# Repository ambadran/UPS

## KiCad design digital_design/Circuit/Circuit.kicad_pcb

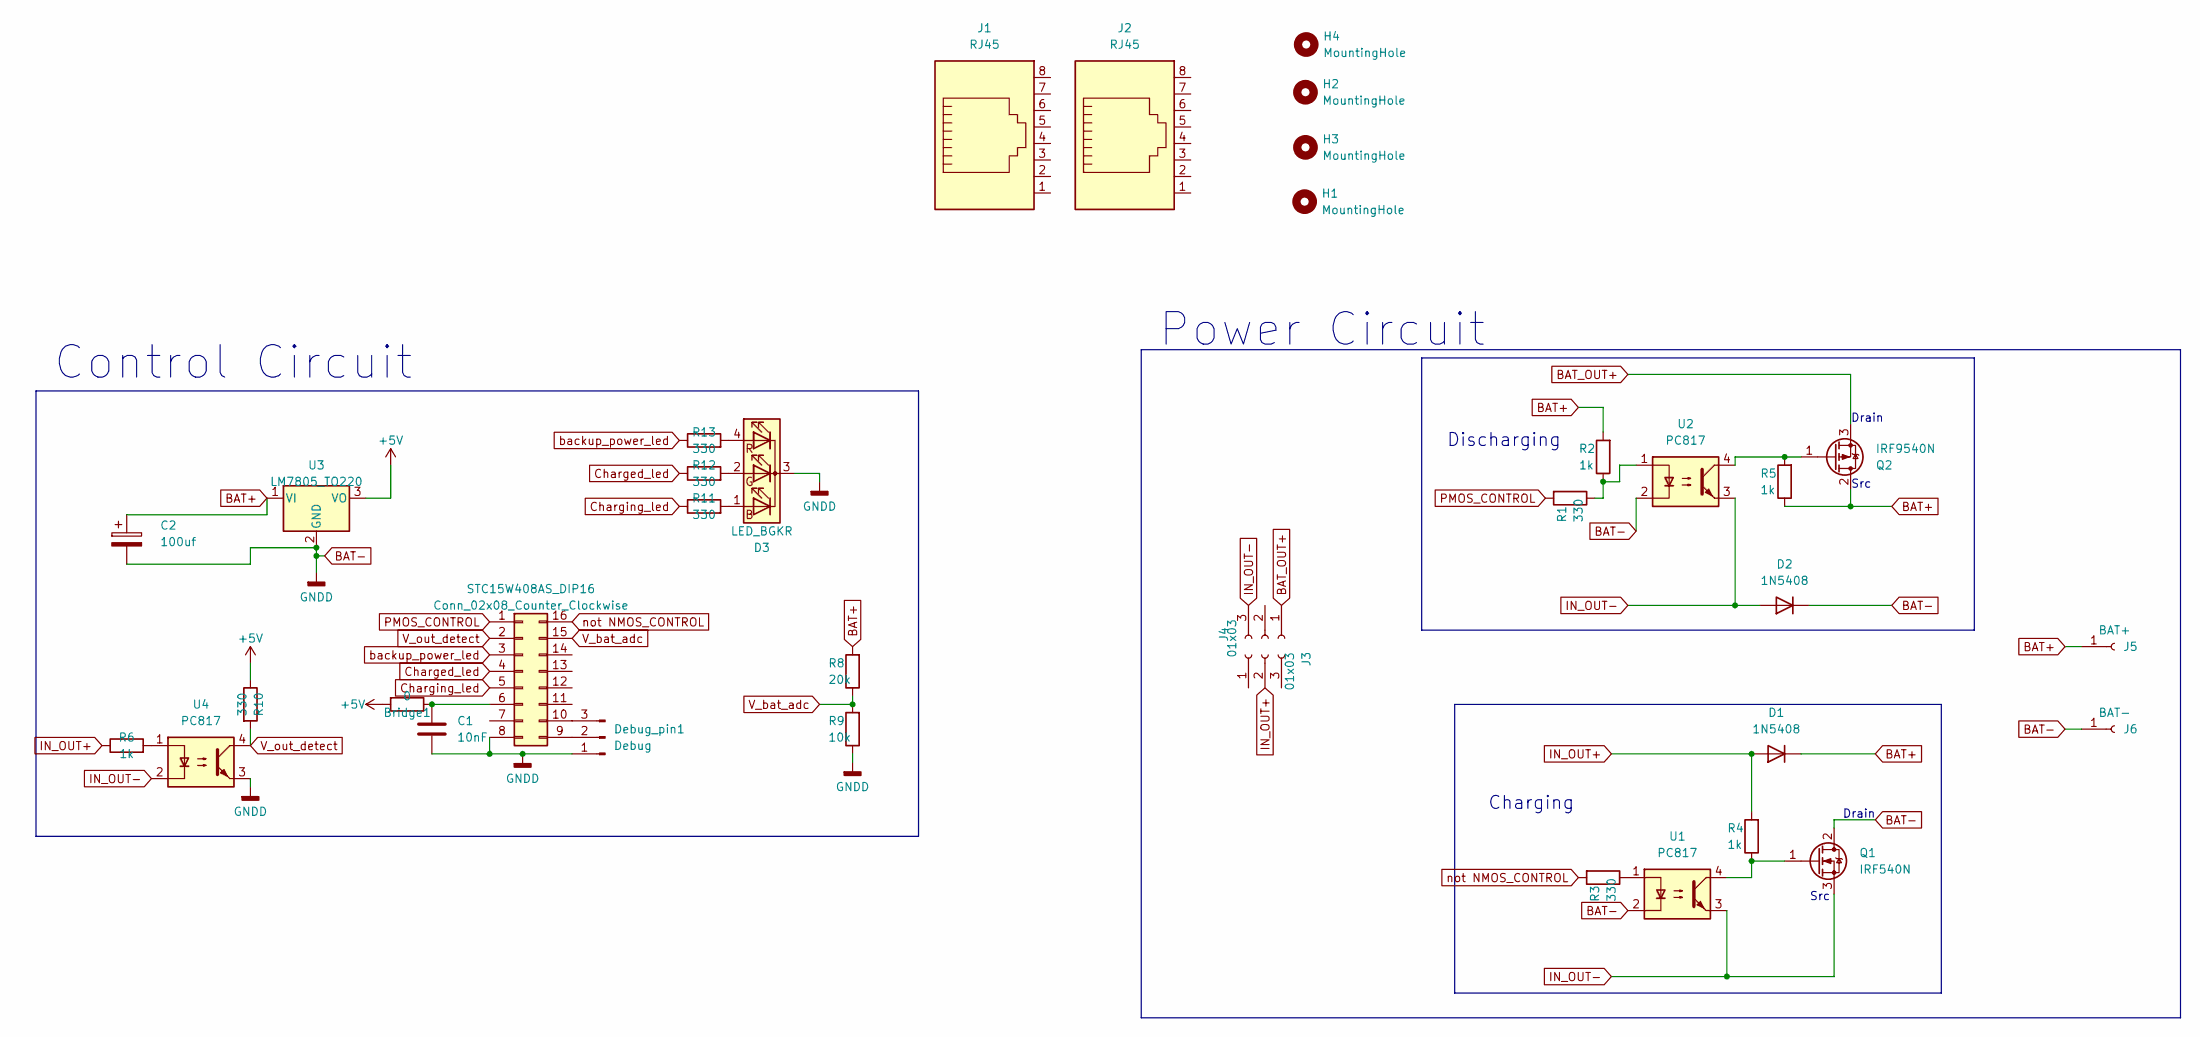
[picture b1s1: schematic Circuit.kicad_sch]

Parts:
Bridge1: 0; R_Axial_DIN0207_L6.3mm_D2.5mm_P7.62mm_Horizontal
C1: 10nF; C_Disc_D5.0mm_W2.5mm_P2.50mm
C2: 100uf; CP_Radial_D5.0mm_P2.50mm
D1, D2: 1N5408; D_DO-201AD_P15.24mm_Horizontal
D3: LED_BGKR; PinSocket_1x04_P2.54mm_Vertical
Debug_pin1: Debug; PinSocket_1x03_P2.54mm_Vertical
H1, H2, H3, H4: MountingHole; MountingHole_4mm_Pad_TopBottom
J1, J2: RJ45; RJ45_OST_PJ012-8P8CX_Vertical
J3, J4: 01x03; SolderWire-0.1sqmm_1x03_P3.6mm_D0.4mm_OD1mm
J5: BAT+; MountingHole_3.2mm_M3_DIN965_Pad_TopBottom
J6: BAT-; MountingHole_3.2mm_M3_DIN965_Pad_TopBottom
Q1: IRF540N; TO-220-3_Vertical
Q2: IRF9540N; TO-220-3_Vertical
R1, R10, R12, R13: 330; R_Axial_DIN0207_L6.3mm_D2.5mm_P7.62mm_Horizontal
R2, R4, R5, R6: 1k; R_Axial_DIN0207_L6.3mm_D2.5mm_P7.62mm_Horizontal
R3, R11: 330; R_Axial_DIN0207_L6.3mm_D2.5mm_P10.16mm_Horizontal
R8: 20k; R_Axial_DIN0207_L6.3mm_D2.5mm_P7.62mm_Horizontal
R9: 10k; R_Axial_DIN0207_L6.3mm_D2.5mm_P7.62mm_Horizontal
STC15W408AS_DIP16: Conn_02x08_Counter_Clockwise; CERDIP-16_W7.62mm_SideBrazed_LongPads
U1, U2, U4: PC817; DIP-4_W7.62mm
U3: LM7805_TO220; TO-220-3_Vertical

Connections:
+5V: Bridge1.2, R10.1, U3.3 (VO)
BAT+: C2.1, D1.1 (K), J5.1, Q2.2 (D), R2.2, R5.1, R8.2, U3.1 (VI)
BAT-: C1.2, C2.2, D2.1 (K), D3.3 (K), Debug_pin1.1, J6.1, Q1.2 (D), R9.1, STC15W408AS_DIP16.8, U1.2, U2.2, U3.2 (GND), U4.3
BAT_OUT+: J4.1, Q2.3 (S)
Charged_led: R12.1, STC15W408AS_DIP16.4
Charging_led: R11.1, STC15W408AS_DIP16.5
IN_OUT+: D1.2 (A), J3.2, R4.2, R6.1
IN_OUT-: D2.2 (A), J4.3, Q1.3 (S), U1.3, U2.3, U4.2
unnamed: D3.1 (BA), R11.2
unnamed: D3.2 (GA), R12.2
unnamed: D3.4 (RA), R13.2
unnamed: Debug_pin1.2, STC15W408AS_DIP16.9
unnamed: Debug_pin1.3, STC15W408AS_DIP16.10
unnamed: Q1.1 (G), R4.1, U1.4
unnamed: Q2.1 (G), R5.2, U2.4
unnamed: R1.1, R2.1, U2.1
unnamed: R3.1, U1.1
unnamed: R6.2, U4.1
unnamed: Bridge1.1, C1.1, STC15W408AS_DIP16.6
PMOS_CONTROL: R1.2, STC15W408AS_DIP16.1
V_bat_adc: R8.1, R9.2, STC15W408AS_DIP16.15
V_out_detect: R10.2, STC15W408AS_DIP16.2, U4.4
backup_power_led: R13.1, STC15W408AS_DIP16.3
not NMOS_CONTROL: R3.2, STC15W408AS_DIP16.16

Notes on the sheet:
Src
Power Circuit
Drain
Control Circuit
Discharging
Charging

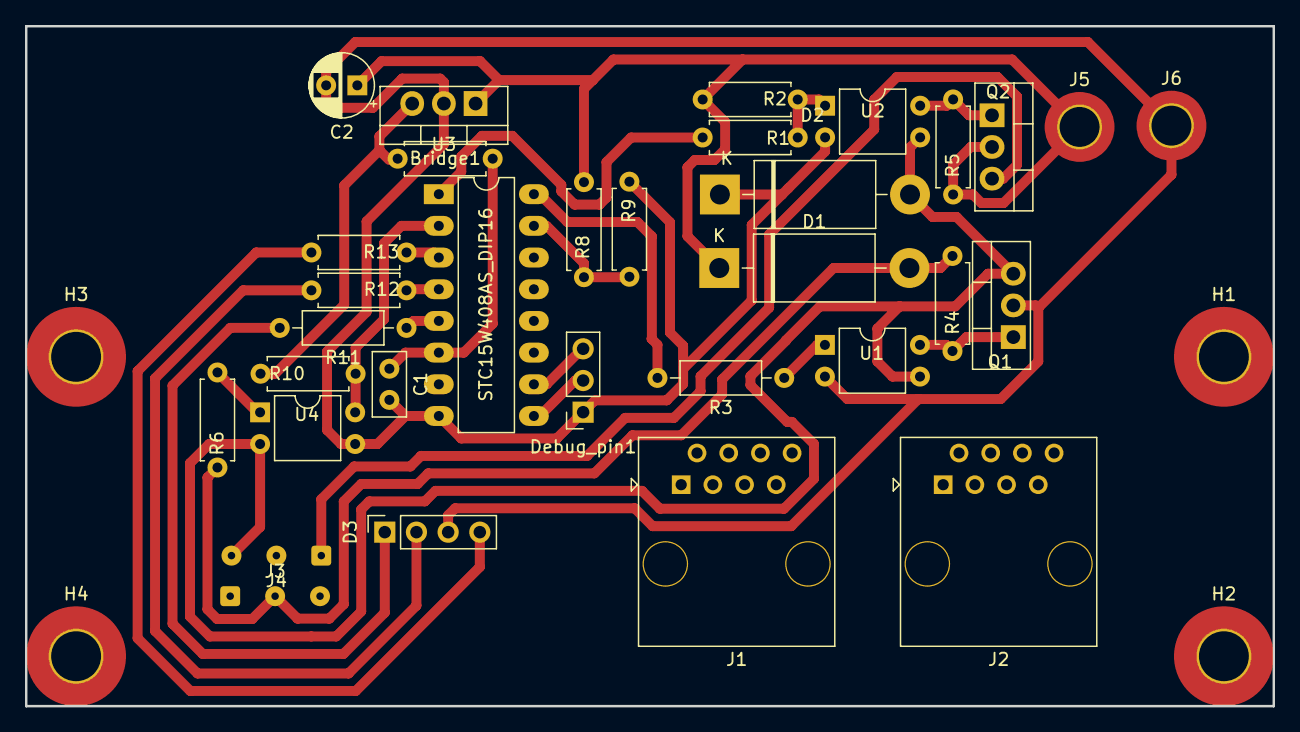
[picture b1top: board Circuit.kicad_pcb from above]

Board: 2 copper layers, 100.0 x 54.5 mm, 36 parts (0 on the bottom side), 24 nets.

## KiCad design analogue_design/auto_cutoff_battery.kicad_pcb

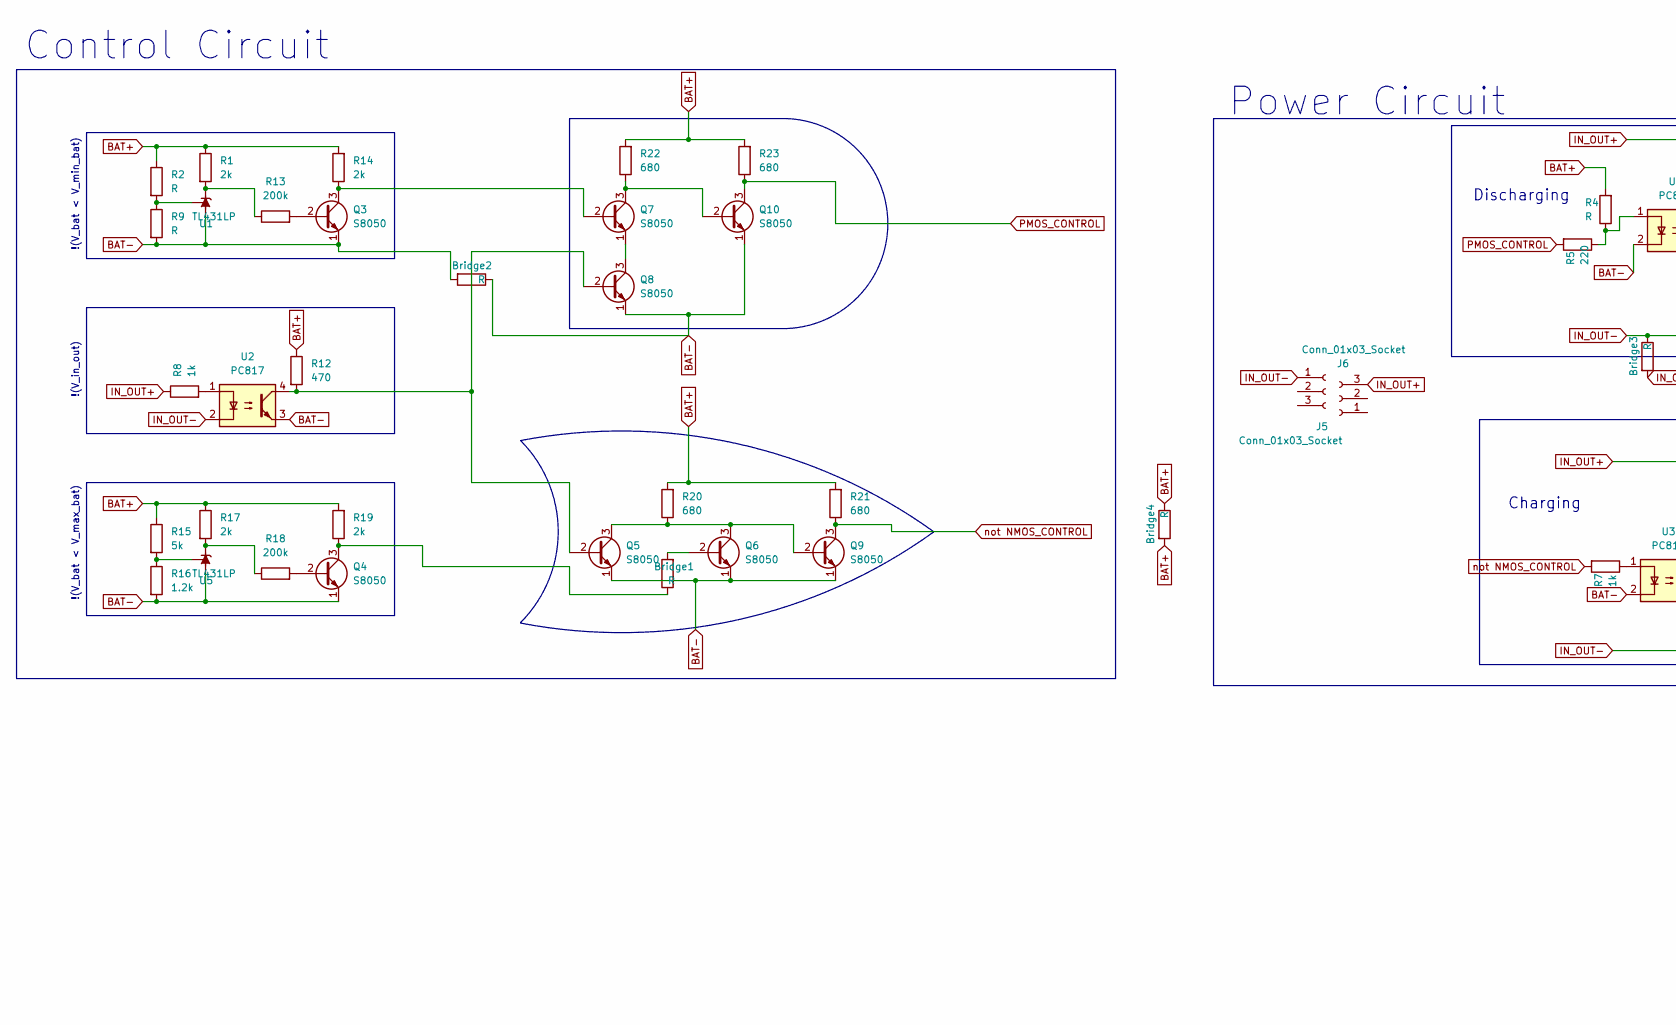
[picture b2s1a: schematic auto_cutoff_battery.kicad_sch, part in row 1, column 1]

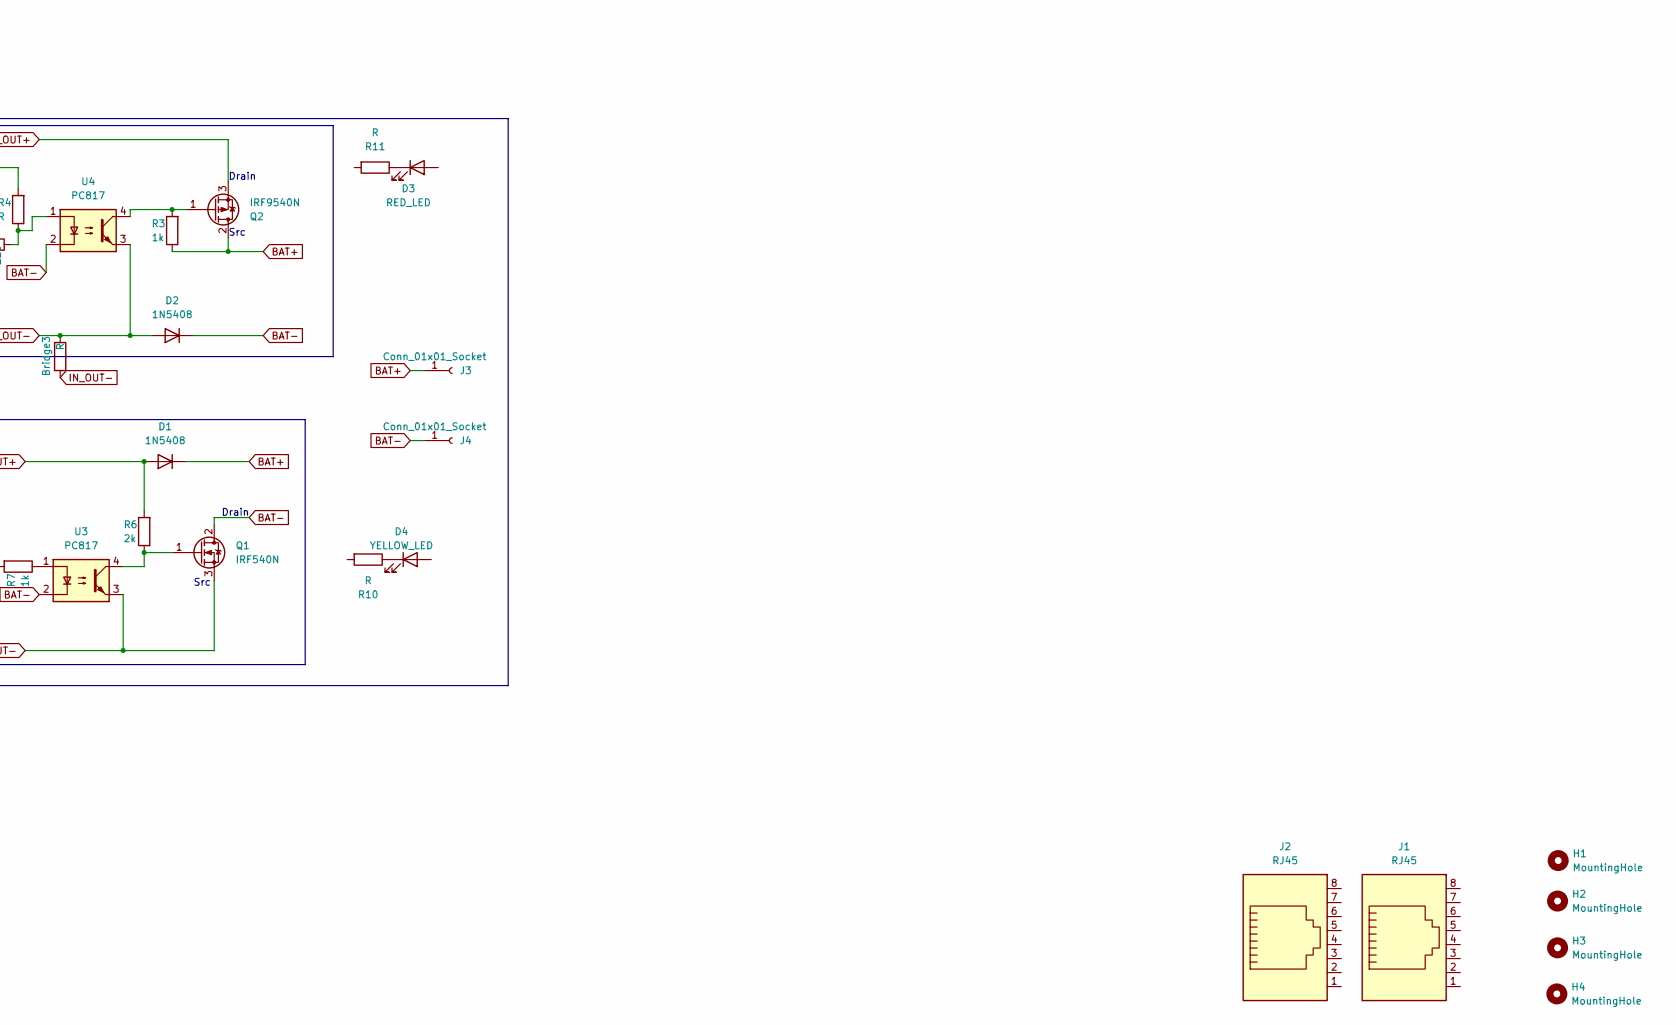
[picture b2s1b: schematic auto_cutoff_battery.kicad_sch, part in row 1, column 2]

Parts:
Bridge1, Bridge2, Bridge3: R; R_Axial_DIN0207_L6.3mm_D2.5mm_P5.08mm_Vertical
Bridge4: R; R_Axial_DIN0207_L6.3mm_D2.5mm_P7.62mm_Horizontal
D1, D2: 1N5408; D_DO-201AD_P15.24mm_Horizontal
D3: RED_LED; LED_D3.0mm
D4: YELLOW_LED; LED_D3.0mm
H1, H2, H3, H4: MountingHole; MountingHole_5.3mm_M5_DIN965_Pad
J1, J2: RJ45; RJ45_Molex_0855135013_Vertical
J3, J4: Conn_01x01_Socket; PinSocket_1x01_P2.54mm_Vertical
J5, J6: Conn_01x03_Socket; SolderWire-0.1sqmm_1x03_P3.6mm_D0.4mm_OD1mm
Q1: IRF540N; TO-220-3_Vertical
Q2: IRF9540N; TO-220-3_Vertical
Q3, Q4, Q5, Q6, Q7, Q8, Q9, Q10: S8050; TO-92_Inline_Wide
R1, R6, R14, R17, R19: 2k; R_Axial_DIN0207_L6.3mm_D2.5mm_P7.62mm_Horizontal
R2, R4, R9, R10, R11: R; R_Axial_DIN0207_L6.3mm_D2.5mm_P7.62mm_Horizontal
R3, R7, R8: 1k; R_Axial_DIN0207_L6.3mm_D2.5mm_P7.62mm_Horizontal
R5: 220; R_Axial_DIN0207_L6.3mm_D2.5mm_P7.62mm_Horizontal
R12: 470; R_Axial_DIN0207_L6.3mm_D2.5mm_P7.62mm_Horizontal
R13, R18: 200k; R_Axial_DIN0207_L6.3mm_D2.5mm_P7.62mm_Horizontal
R15: 5k; R_Axial_DIN0207_L6.3mm_D2.5mm_P7.62mm_Horizontal
R16: 1.2k; R_Axial_DIN0207_L6.3mm_D2.5mm_P7.62mm_Horizontal
R20, R21, R22, R23: 680; R_Axial_DIN0207_L6.3mm_D2.5mm_P7.62mm_Horizontal
U1, U5: TL431LP; TO-92_Inline_Wide
U2, U3, U4: PC817; DIP-4_W7.62mm

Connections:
BAT+: Bridge4.1, Bridge4.2, D1.1 (K), J3.1, Q2.2 (D), R1.1, R2.1, R3.1, R4.2, R12.1, R14.2, R15.1, R17.1, R19.2, R20.2, R21.2, R22.2, R23.2
BAT-: Bridge2.1, Bridge2.2, D2.1 (K), J4.1, Q1.2 (D), Q3.1 (E), Q4.1 (E), Q5.1 (E), Q6.1 (E), Q8.1 (E), Q9.1 (E), Q10.1 (E), R9.2, R16.2, U1.2 (A), U2.3, U3.2, U4.2, U5.2 (A)
IN_OUT+: D1.2 (A), J6.3, Q2.3 (S), R6.2, R8.1
IN_OUT-: Bridge3.1, Bridge3.2, D2.2 (A), J5.1, Q1.3 (S), U2.2, U3.3, U4.3
unnamed: D3.1 (K), R11.1
unnamed: D4.1 (K), R10.1
unnamed: Q1.1 (G), R6.1, U3.4
unnamed: Q2.1 (G), R3.2, U4.4
unnamed: Q3.2 (B), R13.2
unnamed: Q3.3 (C), Q7.2 (B), R14.1
unnamed: Q4.2 (B), R18.2
unnamed: Bridge1.1, Q4.3 (C), R19.1
unnamed: Q5.2 (B), Q8.2 (B), R12.2, U2.4
unnamed: Q5.3 (C), Q6.3 (C), Q9.2 (B), R20.1
unnamed: Bridge1.2, Q6.2 (B)
unnamed: Q7.1 (E), Q8.3 (C)
unnamed: Q7.3 (C), Q10.2 (B), R22.1
unnamed: R4.1, R5.1, U4.1
unnamed: R7.1, U3.1
unnamed: R8.2, U2.1
unnamed: R1.2, R13.1, U1.3 (K)
unnamed: R2.2, R9.1, U1.1 (REF)
unnamed: R17.2, R18.1, U5.3 (K)
unnamed: R15.2, R16.1, U5.1 (REF)
PMOS_CONTROL: Q10.3 (C), R5.2, R23.1
not NMOS_CONTROL: Q9.3 (C), R7.2, R21.1

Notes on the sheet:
Discharging
Drain
Control Circuit
Src
!(V_bat < V_min_bat)
Charging
!(V_in_out)
Power Circuit
!(V_bat < V_max_bat)

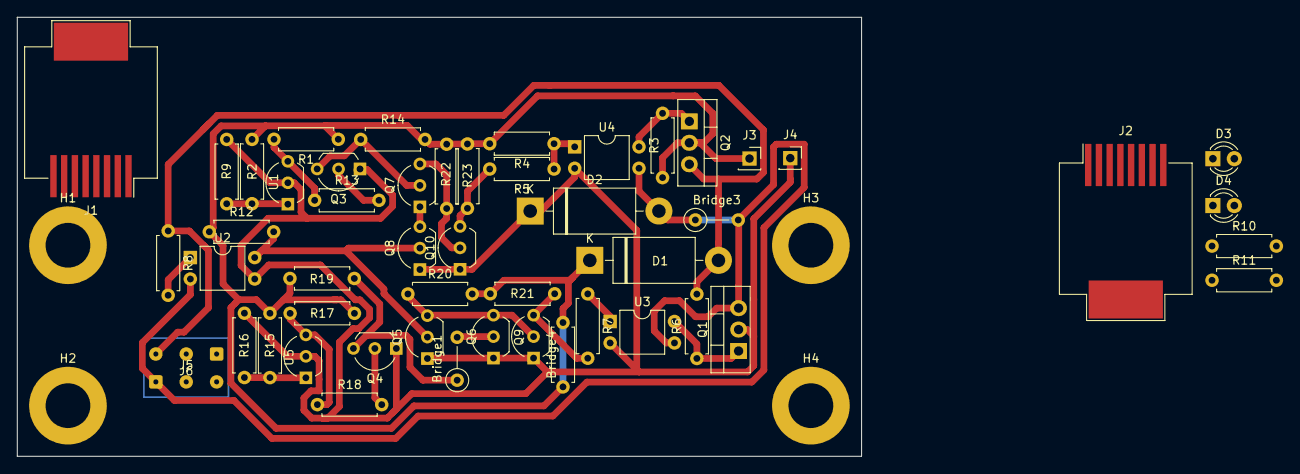
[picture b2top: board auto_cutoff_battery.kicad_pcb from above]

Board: 2 copper layers, 100.0 x 52.0 mm, 55 parts (0 on the bottom side), 26 nets.

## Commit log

2024-04-26 added digital circuit schematic
2024-04-26 minor change in power electronics schematic
2024-04-27 minor changes
2024-04-27 started PCB design
2024-04-28 finished PCB solution
2024-04-29 started final design
2024-04-29 finished PCB and added gcode files
2024-05-01 added resistor values
2024-05-02 finished V1
2024-05-02 added final BOM
2024-05-06 started updating
2024-05-07 Updated Design as per requirement
2024-05-10 changed holes footprint
